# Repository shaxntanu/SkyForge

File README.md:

# SkyForge
Flight Controller using ESP 32 and Gyroscope based on Git City Plane Simulator

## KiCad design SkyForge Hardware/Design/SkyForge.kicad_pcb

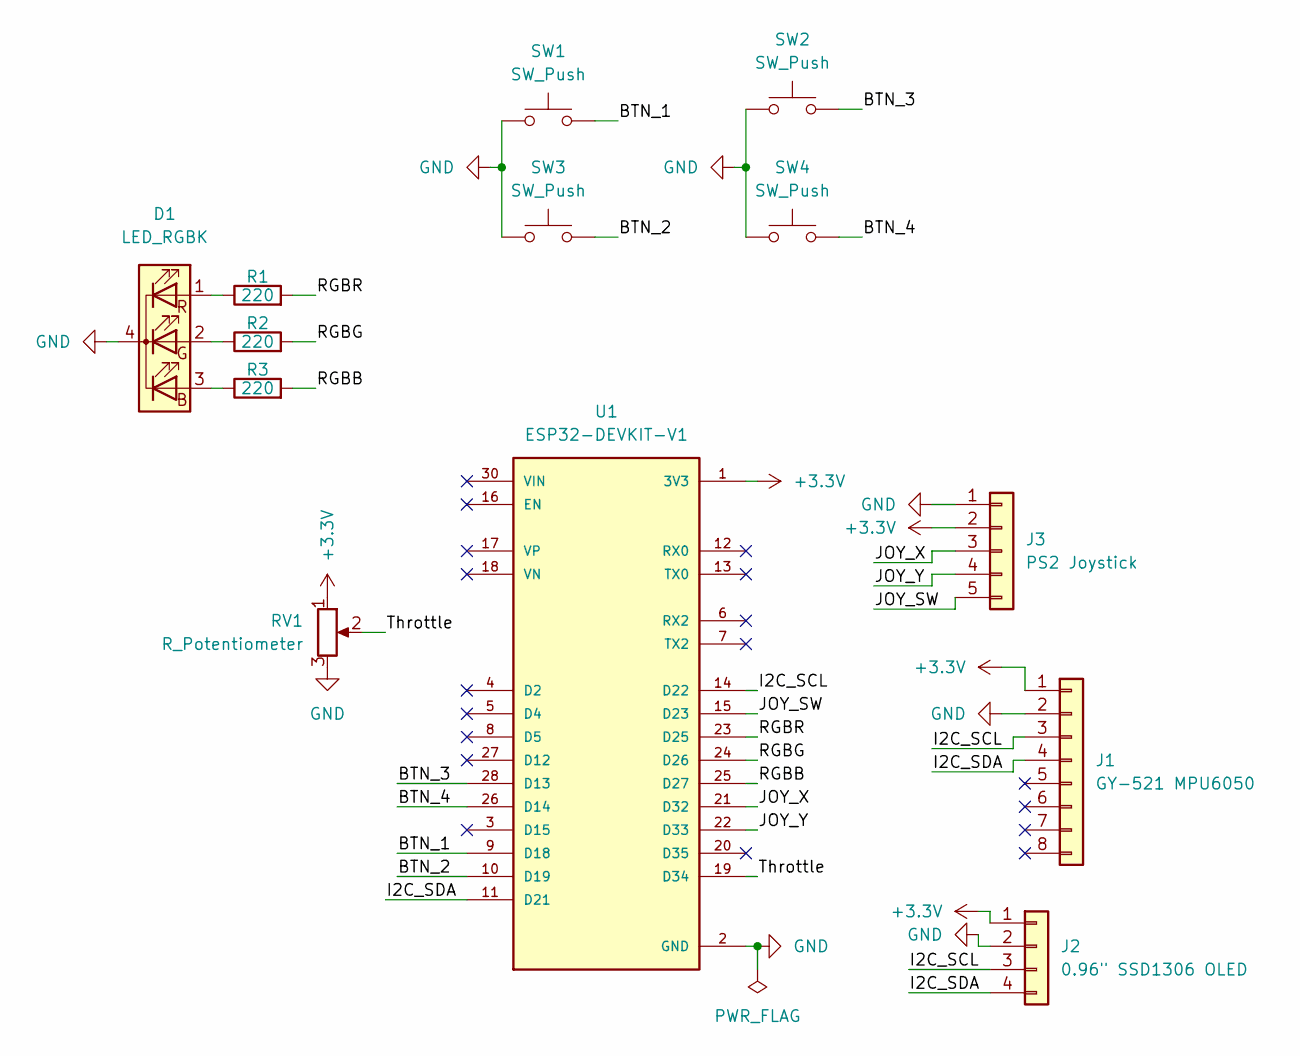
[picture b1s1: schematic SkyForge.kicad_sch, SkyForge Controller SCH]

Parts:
D1: LED_RGBK; LED_D5.0mm-4_RGB
J1: GY-521 MPU6050; PinSocket_1x08_P2.54mm_Vertical
J2: 0.96" SSD1306 OLED; PinSocket_1x04_P2.54mm_Vertical
J3: PS2 Joystick; PinSocket_1x05_P2.54mm_Vertical
R1, R2, R3: 220; R_Axial_DIN0207_L6.3mm_D2.5mm_P10.16mm_Horizontal
RV1: R_Potentiometer; Potentiometer_Alps_RK09K_Single_Horizontal
SW1, SW2, SW3, SW4: SW_Push; SW_PUSH-12mm
U1: ESP32-DEVKIT-V1; MODULE_ESP32_DEVKIT_V1; PARTREV N/A

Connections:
+3.3V: J1.1, J2.1, J3.2, RV1.1, U1.1 (3V3)
/BTN_1: SW1.2, U1.9 (D18)
/BTN_2: SW3.2, U1.10 (D19)
/BTN_3: SW2.2, U1.28 (D13)
/BTN_4: SW4.2, U1.26 (D14)
/I2C_SCL: J1.3, J2.3, U1.14 (D22)
/I2C_SDA: J1.4, J2.4, U1.11 (D21)
/JOY_SW: J3.5, U1.15 (D23)
/JOY_X: J3.3, U1.21 (D32)
/JOY_Y: J3.4, U1.22 (D33)
/RGBB: R3.2, U1.25 (D27)
/RGBG: R2.2, U1.24 (D26)
/RGBR: R1.2, U1.23 (D25)
/Throttle: RV1.2, U1.19 (D34)
GND: D1.4 (K), J1.2, J2.2, J3.1, RV1.3, SW1.1, SW2.1, SW3.1, SW4.1, U1.2 (GND), U1.29 (GND)
unnamed: D1.3 (BA), R3.1
unnamed: D1.2 (GA), R2.1
unnamed: D1.1 (RA), R1.1

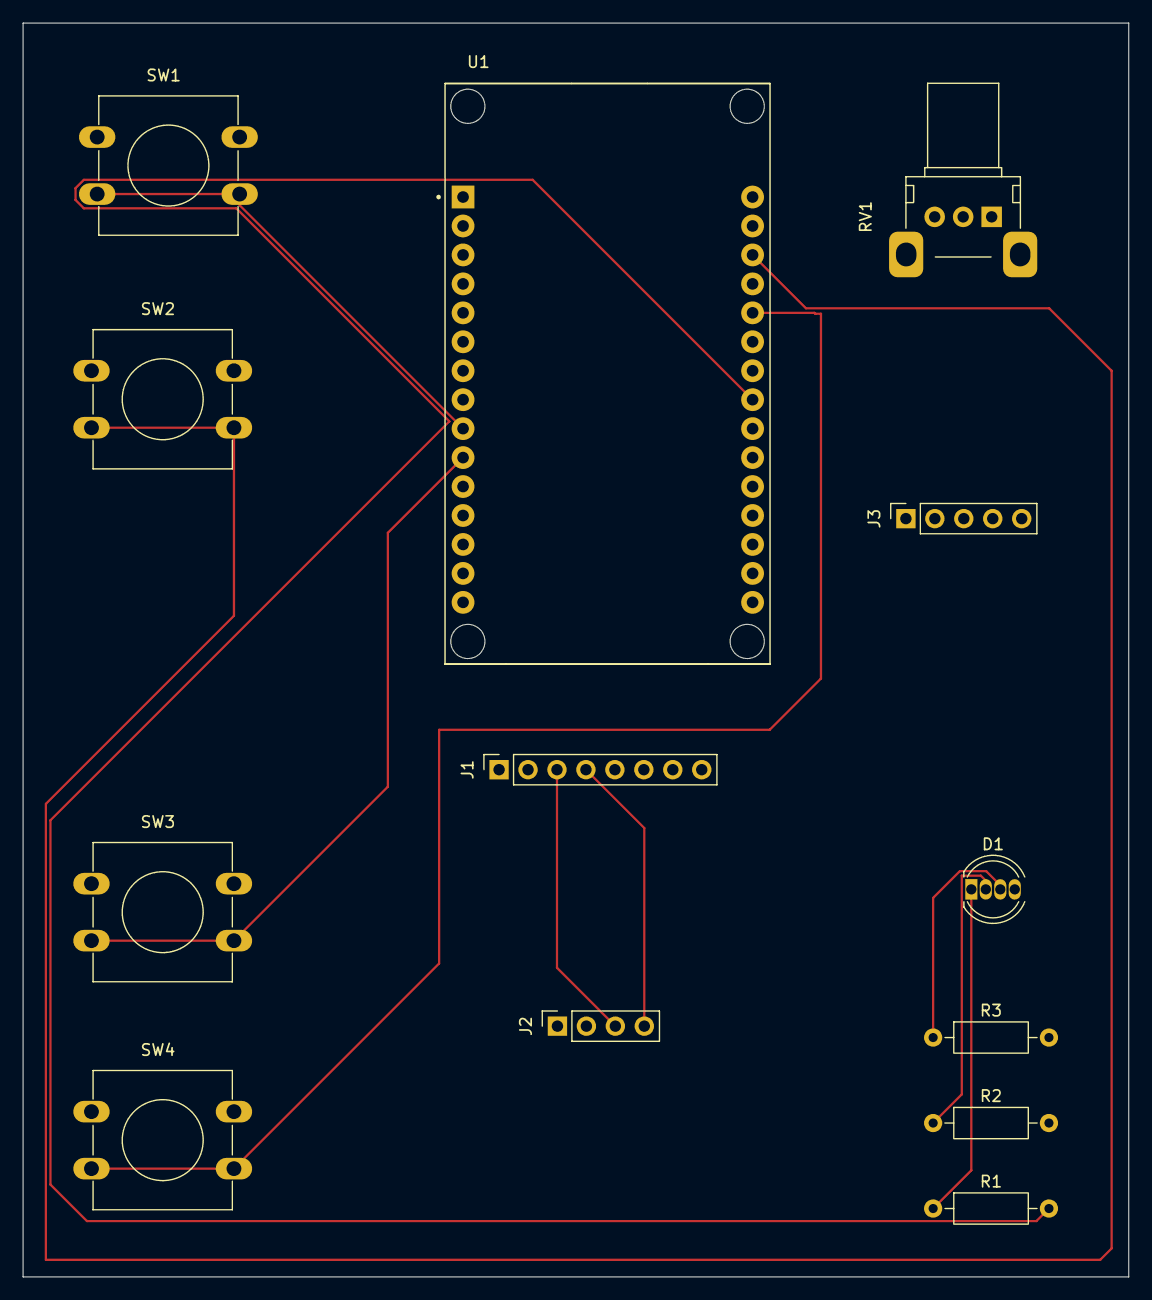
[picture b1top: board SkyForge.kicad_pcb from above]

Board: 4 copper layers, 97.0 x 110.0 mm, 13 parts (0 on the bottom side), 18 nets.
